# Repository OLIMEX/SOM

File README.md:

=System on Module=

This is the GitHub repository for Olimex System on Module (SOM) boards resources hardware and software.

OLIMEX System-on-Module (SOM) boards are powerful Linux-capable boards. They follow a low-cost modular design which allows rapid product development. Each of these boards has two parts - a main part which nests the processor, the memory and the power control unit; and a peripheral part which contains the USB ports, the video output and most of the connectors. SOM designs are targeted at customers who want to apply custom modifications and own solutions based on a specific processor without having to deal with multi layer PCBs with controlled impedance and BGA assembly. This makes it possible to create simpler boards (that might be manufactured by your local board manufacturer) containing only the peripherals you need with the dimensions and shape suitable for your specific solution.

Both the main part and the peripheral part of the SOM system have support in the official Android and Debian images distributed by Olimex and maintained by Olimex and the Linux community.

The peripheral part of the SOM design is considered Open Source HardWare (OSHW) and the customer has access to the board source files that we used to manufacture it. The part of the design that has the main microcontroller is considered proprietary design and design files would not be shared. The official Android and Debian images released for the SOM boards are open software. We usually try to provide step-by-step instructions on how we have compiled the images. These instructions might be found at the olimex wordpress page. 

If you are looking for the open source hardware design of the processors used, please, check the OLinuXino boards. OLinuXino board designs are fully open source hradware but harder to implement in own solutions and require more of a hardware experience to do so. Nevertheless OLinuXino boards are pretty good choice for evaluating the capabilities of the embedded processors.

At the moment Olimex deals with the following categories of SOM boards:

==Allwinner A13==

==Allwinner A20==

==Texas Instruments AM3352==

==Rockchip RK3188==

==Rockchip RK3328==

==STM STM32MP153==

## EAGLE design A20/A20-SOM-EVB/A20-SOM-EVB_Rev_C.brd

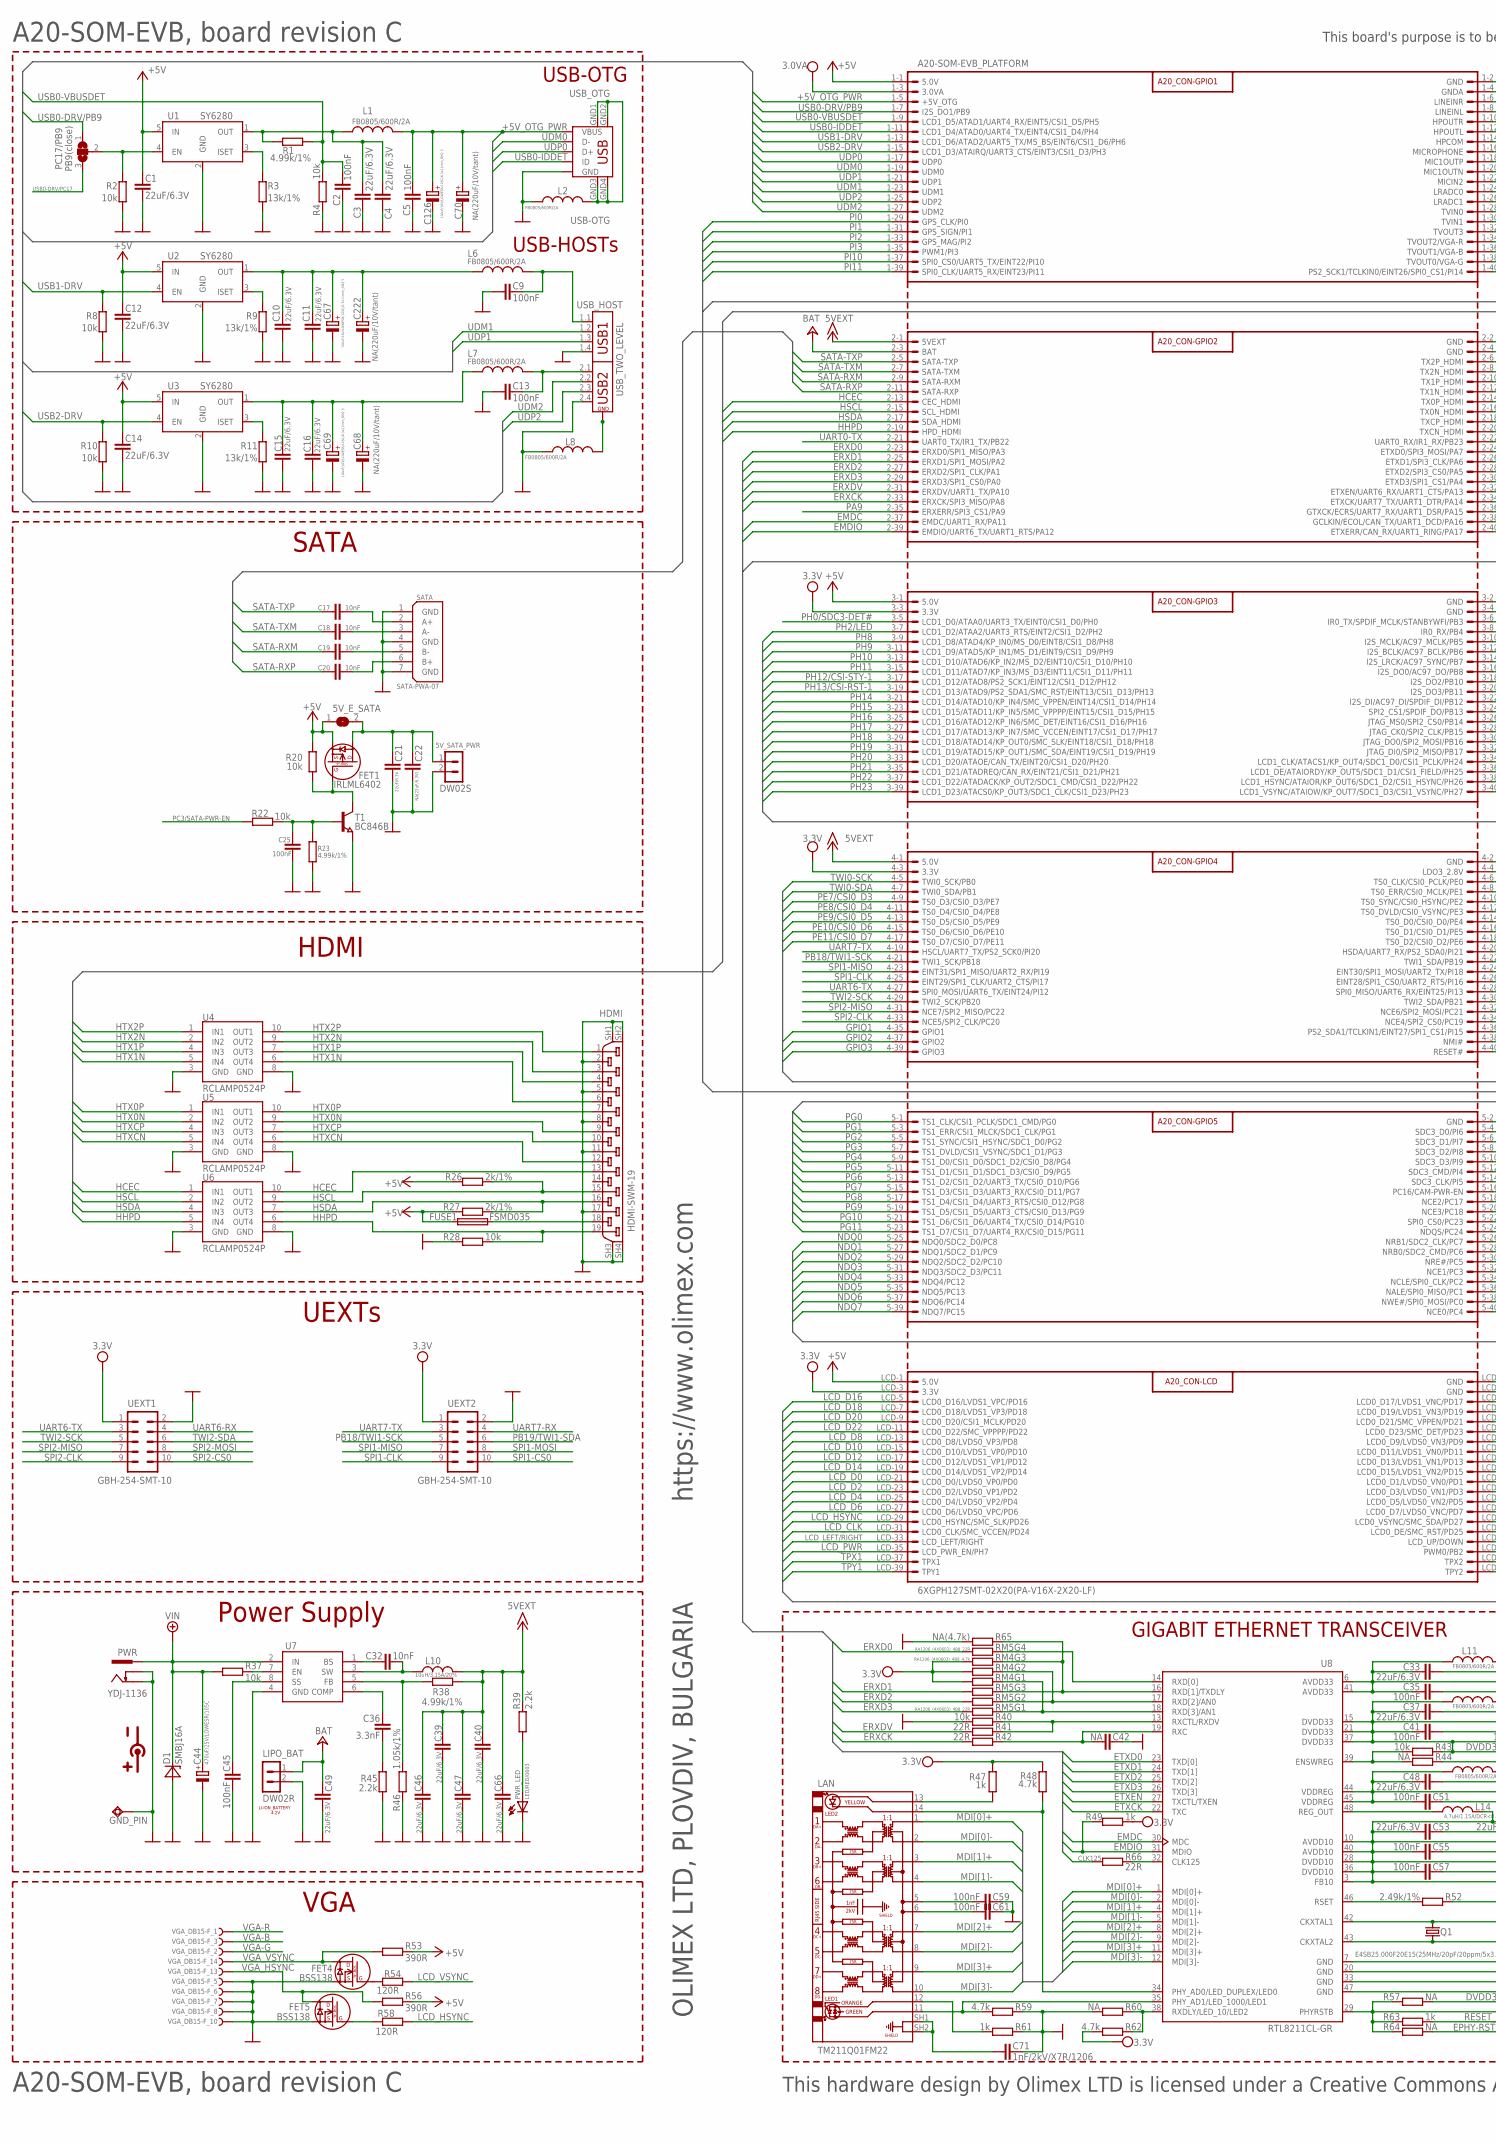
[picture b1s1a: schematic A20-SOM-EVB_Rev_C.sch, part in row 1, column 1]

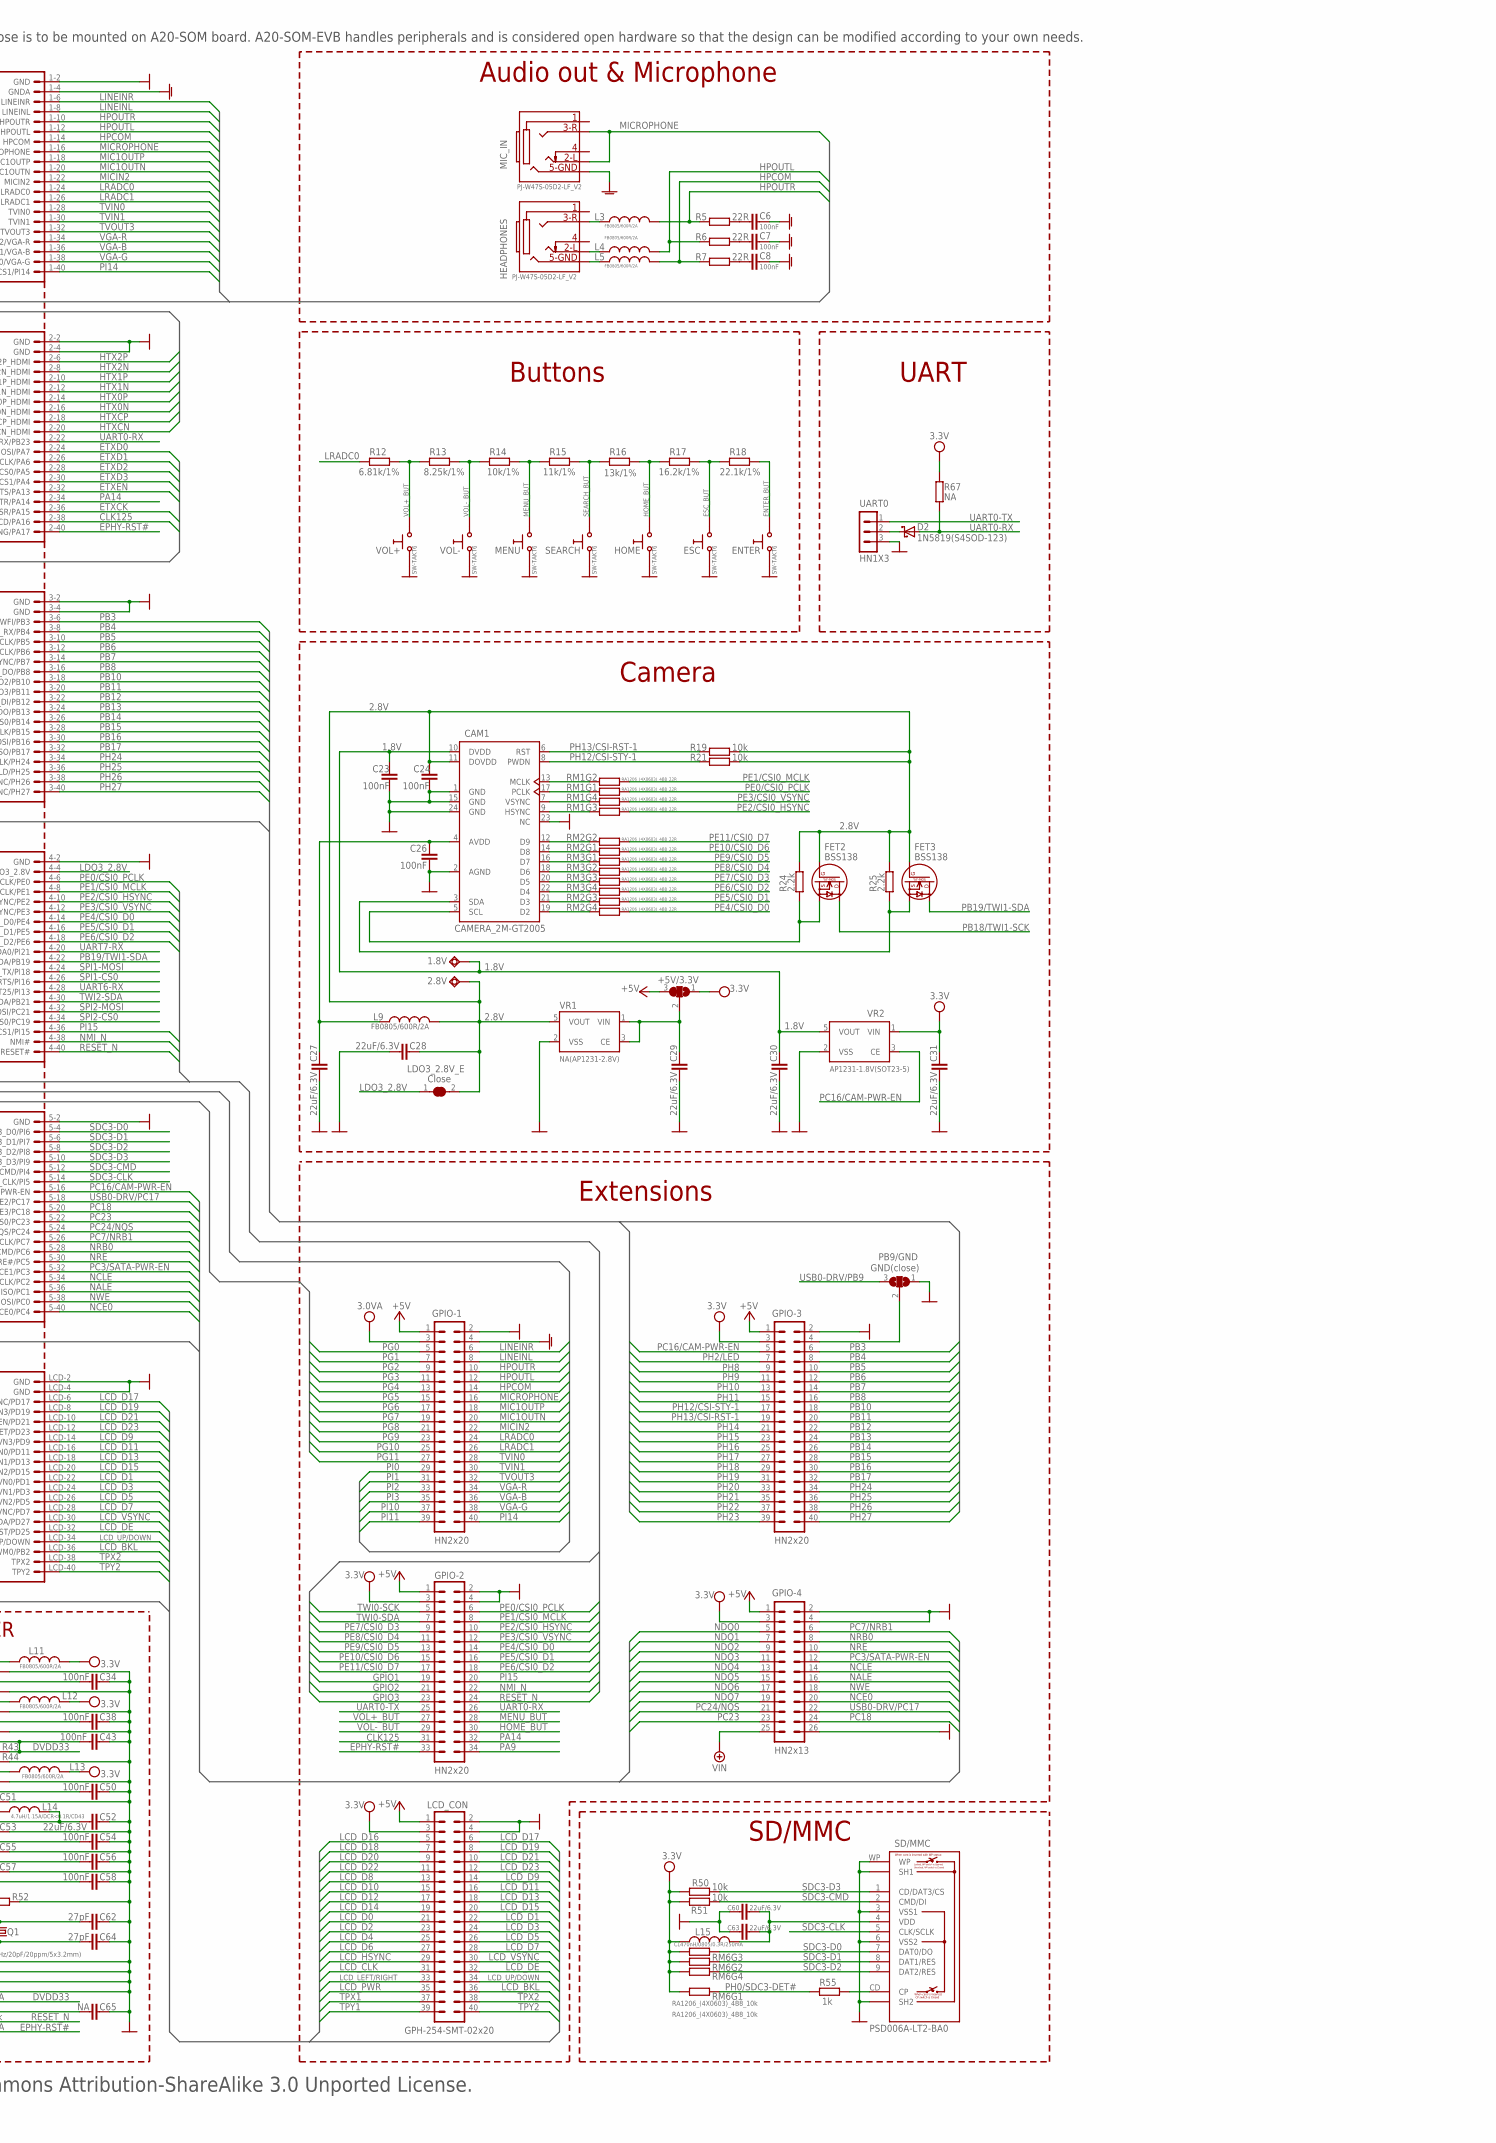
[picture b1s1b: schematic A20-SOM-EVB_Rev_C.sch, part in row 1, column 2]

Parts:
1.8V, 2.8V: TESTPAD80/40; SMD80/40
5V_E_SATA: SJSJ_SMALLER; SJ_1_SMALLER
5V_SATA_PWR: DW02S
+5V/3.3V: SJ2W8; SJ_2_SMALLER_23_TIED
A20-SOM-EVB_PLATFORM: 6XGPH127SMT-02X20(PA-V16X-2X20-LF); A20-SOM-EVB
C1, C3, C4, C10, C11, C12, C14, C15, C16, C21, C27, C28, C29, C30, C31, C33, C37, C39, C40, C46, C47, C48, C49, C52, C53, C60, C63, C66: 22uF/6.3V; C0603_DWS
C2, C5, C6, C7, C8, C9, C13, C23, C24, C25, C26, C34, C35, C38, C41, C43, C45, C50, C51, C54, C55, C56, C57, C58, C59, C61: 100nF; C0603_DWS
C17, C18, C19, C20, C32: 10nF; C0603_DWS
C22: NA(22uF/6.3V); C0603_DWS
C36: 3.3nF; C0603_DWS
C42, C65: NA; C0603_DWS
C44: 470uF/25V/LOWESR/105C; E3,5-8
C62, C64: 27pF; C0603_DWS
C67, C69, C126: 100uF/16V/LOWESR/105C/6.3x11mm_RM2.5; E2,5-6,3
C68, C70, C222: NA(220uF/10V/tant); CT7343
C71: 1nF/2kV/X7R/1206; C1206_5MILS_WS_ISO
CAM1: CAMERA_2M-GT2005; CAM_2M_GT2005
D1: SMBJ16A; DO214AA
D2: 1N5819(S4SOD-123); SOD-123
ENTER: SW-TAKT6; SW-TAKT_6X3.5_SMD
ESC: SW-TAKT6; SW-TAKT_6X3.5_SMD
FET1: IRLML6402; SOT23
FET2, FET3, FET4, FET5: BSS138; SOT23
FUSE1: FSMD035; 1206
GND_PIN: TESTPAD3; TEST_PAD40/70/SQUARE
GPIO-1, GPIO-3: HN2x20; ML40-MALE(GBH-254-SMT-40)
GPIO-2: HN2x20; ML34-MALE(GBH-254-SMT-34)
GPIO-4: HN2x13; ML26-MALE(GBH-254-SMT-26)
HDMI: HDMI-SWM-19
HEADPHONES: PJ-W47S-05D2-LF_V2; PJ-W47S-05D2-LF_5PIN_V2
HOME: SW-TAKT6; SW-TAKT_6X3.5_SMD
L1, L2, L3, L4, L5, L6, L7, L8, L9, L11, L12, L13: FB0805/600R/2A; L0805_5MIL_DWS
L10: 10uH/3.15A/20%; 8X7MM_3131
L14: 4.7uH/1.15A/DCR<0.1R/CD43; CD42(43)
L15: CL470nH/0805/0.3R/250mA; L0805_5MIL_DWS
LAN: TM211Q01FM22; TM211Q01FM22_SH
LCD_CON: GPH-254-SMT-02x20; ML40-MALE(GBH-254-SMT-40)
LDO3_2.8V_E: Close; SJ_1_SMALLER_CLOSE
LIPO_BAT: DW02R
MENU: SW-TAKT6; SW-TAKT_6X3.5_SMD
MIC_IN: PJ-W47S-05D2-LF_V2; PJ-W47S-05D2-LF_5PIN_V2
PB9/GND: GND(close); SJ_2_SMALL
PC17/PB9: PB9(close); SJ_2_SMALL
PWR: YDJ-1136; PWR_JACK_UNI_MILLING
PWR_LED: LED/RED/0603; LED-0603
Q1: E4SB25.000F20E15(25MHz/20pF/20ppm/5x3.2mm); HCX-4S
R1, R23, R38: 4.99k/1%; R0603_5MIL_DWS
R2, R4, R8, R10, R19, R20, R21, R22, R28, R37, R40, R43, R50, R51: 10k; R0603_5MIL_DWS
R3, R9, R11, R16: 13k/1%; R0603_5MIL_DWS
R5, R6, R7, R41, R42, R66: 22R; R0603_5MIL_DWS
R12: 6.81k/1%; R0603_5MIL_DWS
R13: 8.25k/1%; R0603_5MIL_DWS
R14: 10k/1%; R0603_5MIL_DWS
R15: 11k/1%; R0603_5MIL_DWS
R17: 16.2k/1%; R0603_5MIL_DWS
R18: 22.1k/1%; R0603_5MIL_DWS
R24, R25, R39, R45: 2.2k; R0603_5MIL_DWS
R26, R27: 2k/1%; R0603_5MIL_DWS
R44, R57, R60, R64, R67: NA; R0603_5MIL_DWS
R46: 1.05k/1%; R0603_5MIL_DWS
R47, R49, R55, R61, R63: 1k; R0603_5MIL_DWS
R48, R59, R62: 4.7k; R0603_5MIL_DWS
R52: 2.49k/1%; R0603_5MIL_DWS
R53, R56: 390R; R0603_5MIL_DWS
R54, R58: 120R; R0603_5MIL_DWS
R65: NA(4.7k); R0603_5MIL_DWS
RM1, RM2, RM3, RM5: RA1206_(4X0603)_4B8_22R; R_MATRIX_4
RM4: RA1206_(4X0603)_4B8_4.7k; R_MATRIX_4
RM6: RA1206_(4X0603)_4B8_10k; R_MATRIX_4
SATA: SATA-PWA-07
SD/MMC: PSD006A-LT2-BA0; SD_CARD
SEARCH: SW-TAKT6; SW-TAKT_6X3.5_SMD
T1: BC846B; SOT23
U1, U2, U3: SY6280; SOT23-5
U4, U5, U6: RCLAMP0524P; SLP2510P8
U7: MP1482DS; SOIC8
U8: RTL8211CL-GR; LQFP48
UART0: HN1X3
UEXT1, UEXT2: GBH-254-SMT-10; ML10_S
USB_HOST: USB_TWO_LEVEL
USB_OTG: USB-OTG; USB_MINI_9PIN
VGA_DB15-F: VGA15; DB15-F_22MM
VOL+: SW-TAKT6; SW-TAKT_6X3.5_SMD
VOL-: SW-TAKT6; SW-TAKT_6X3.5_SMD
VR1: NA(AP1231-2.8V); SOT-23-5
VR2: AP1231-1.8V(SOT23-5); SOT-23-5

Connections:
1.8V: 1.8V.P$1, C23.1, C30.1, CAM1.10 (DVDD), VR2.5 (VOUT)
2.8V: 2.8V.P$1, C24.1, C28.1, CAM1.11 (DOVDD), FET2.1 (G), FET3.1 (G), L9.2, LDO3_2.8V_E.2, R19.2, R21.2, R24.2, R25.2, VR1.5 (VOUT)
+5V: 5V_E_SATA.1, +5V/3.3V.3, A20-SOM-EVB_PLATFORM.1-1 (5.0V), A20-SOM-EVB_PLATFORM.3-1 (5.0V), A20-SOM-EVB_PLATFORM.LCD-1 (5.0V), C1.1, C12.1, C14.1, FET1.2 (S), FUSE1.1, GPIO-1.1, GPIO-2.1, GPIO-3.1, GPIO-4.1, LCD_CON.1, R20.1, R26.2, R27.2, R53.1, R56.1, U1.5 (IN), U2.5 (IN), U3.5 (IN)
+5V_OTG_PWR: A20-SOM-EVB_PLATFORM.1-5 (+5V_OTG), C5.1, C70.+, C126.+, L1.1, USB_OTG.VBUS
+12V: C44.+, D1.C, GPIO-4.25, PWR.+, R37.1, U7.2 (IN)
+15V: A20-SOM-EVB_PLATFORM.2-1 (5VEXT), A20-SOM-EVB_PLATFORM.4-1 (5.0V), C39.1, C40.1, C46.1, C47.1, C66.1, L10.2, R38.2, R39.1
+24V: A20-SOM-EVB_PLATFORM.2-3 (BAT), C49.2, LIPO_BAT.1
AVDD1: C26.1, C27.1, CAM1.4 (AVDD), L9.1
AVDD33: C33.2, C34.2, C35.2, L11.2, U8.6 (AVDD33), U8.41 (AVDD33)
AVDD/DVDD(1.05V): C52.2, C53.2, C54.2, C55.2, C56.2, C57.2, C58.2, L14.2, U8.3 (FB10), U8.10 (AVDD10), U8.28 (DVDD10), U8.36 (DVDD10), U8.40 (AVDD10)
CLK125: A20-SOM-EVB_PLATFORM.2-38 (GCLKIN/ECOL/CAN_TX/UART1_DCD/PA16), GPIO-2.31, R66.1
DVDD33: C37.2, C38.2, C41.2, C43.2, L12.2, R43.1, R57.1, U8.15 (DVDD33), U8.21 (DVDD33), U8.37 (DVDD33)
EMDC: A20-SOM-EVB_PLATFORM.2-37 (EMDC/UART1_RX/PA11), U8.30 (MDC)
EMDIO: A20-SOM-EVB_PLATFORM.2-39 (EMDIO/UART6_TX/UART1_RTS/PA12), R49.1, U8.31 (MDIO)
ENTER_BUT: ENTER.P$2 (1), R18.2
EPHY-RST#: A20-SOM-EVB_PLATFORM.2-40 (ETXERR/CAN_RX/UART1_RING/PA17), GPIO-2.33, R64.1
ERXCK: A20-SOM-EVB_PLATFORM.2-33 (ERXCK/SPI3_MISO/PA8), R42.2
ERXD0: A20-SOM-EVB_PLATFORM.2-23 (ERXD0/SPI1_MISO/PA3), RM5.4.2 (2)
ERXD1: A20-SOM-EVB_PLATFORM.2-25 (ERXD1/SPI1_MOSI/PA2), RM5.3.2 (2)
ERXD2: A20-SOM-EVB_PLATFORM.2-27 (ERXD2/SPI1_CLK/PA1), RM5.2.2 (2)
ERXD3: A20-SOM-EVB_PLATFORM.2-29 (ERXD3/SPI1_CS0/PA0), RM5.1.2 (2)
ERXDV: A20-SOM-EVB_PLATFORM.2-31 (ERXDV/UART1_TX/PA10), R41.2
ESC_BUT: ESC.P$2 (1), R17.2, R18.1
ETXCK: A20-SOM-EVB_PLATFORM.2-36 (GTXCK/ECRS/UART7_RX/UART1_DSR/PA15), U8.22 (TXC)
ETXD0: A20-SOM-EVB_PLATFORM.2-24 (ETXD0/SPI3_MOSI/PA7), U8.23 (TXD[0])
ETXD1: A20-SOM-EVB_PLATFORM.2-26 (ETXD1/SPI3_CLK/PA6), U8.24 (TXD[1])
ETXD2: A20-SOM-EVB_PLATFORM.2-28 (ETXD2/SPI3_CS0/PA5), U8.25 (TXD[2])
ETXD3: A20-SOM-EVB_PLATFORM.2-30 (ETXD3/SPI1_CS1/PA4), U8.26 (TXD[3])
ETXEN: A20-SOM-EVB_PLATFORM.2-32 (ETXEN/UART6_RX/UART1_CTS/PA13), U8.27 (TXCTL/TXEN)
GND: 5V_SATA_PWR.2, A20-SOM-EVB_PLATFORM.1-2 (GND), A20-SOM-EVB_PLATFORM.2-2 (GND), A20-SOM-EVB_PLATFORM.2-4 (GND), A20-SOM-EVB_PLATFORM.3-2 (GND), A20-SOM-EVB_PLATFORM.3-4 (GND), A20-SOM-EVB_PLATFORM.4-2 (GND), A20-SOM-EVB_PLATFORM.5-2 (GND), A20-SOM-EVB_PLATFORM.LCD-2 (GND), A20-SOM-EVB_PLATFORM.LCD-4 (GND), C1.2, C2.2, C3.2, C4.2, C5.2, C9.2, C10.2, C11.2, C12.2, C13.2, C14.2, C15.2, C16.2, C21.1, C22.1, C23.2, C24.2, C25.2, C26.2, C27.2, C28.2, C29.2, C30.2, C31.2, C33.1, C34.1, C35.1, C37.1, C38.1, C39.2, C40.2, C41.1, C42.2, C43.1, C44.-, C45.2, C46.2, C47.2, C48.1, C49.1, C50.1, C51.1, C52.1, C53.1, C54.1, C55.1, C56.1, C57.1, C58.1, C59.1, C60.1, C61.1, C62.1, C63.1, C64.1, C65.1, C66.2, C67.-, C68.-, C69.-, C70.-, C71.1, C126.-, C222.-, CAM1.1 (GND), CAM1.2 (AGND), CAM1.15 (GND), CAM1.23 (NC), CAM1.24 (GND), D1.A, ENTER.P$1 (0), ESC.P$1 (0), FET4.2 (S), FET5.2 (S), GND_PIN.P$1, GPIO-1.2, GPIO-2.2, GPIO-2.4, GPIO-3.2, GPIO-4.2, GPIO-4.4, GPIO-4.26, HDMI.2, HDMI.5, HDMI.8, HDMI.11, HDMI.17, HDMI.SH1 (20), HDMI.SH2 (21), HDMI.SH3 (22), HDMI.SH4 (23), HOME.P$1 (0), L2.1, L8.1, LCD_CON.2, LCD_CON.4, LIPO_BAT.2, MENU.P$1 (0), PB9/GND.1, PWR.-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
GNDA: A20-SOM-EVB_PLATFORM.1-4 (GNDA), C6.1, C7.1, C8.1, GPIO-1.4, MIC_IN.5
GPIO1: A20-SOM-EVB_PLATFORM.4-35 (GPIO1), GPIO-2.19
GPIO2: A20-SOM-EVB_PLATFORM.4-37 (GPIO2), GPIO-2.21
GPIO3: A20-SOM-EVB_PLATFORM.4-39 (GPIO3), GPIO-2.23
HCEC: A20-SOM-EVB_PLATFORM.2-13 (CEC_HDMI), HDMI.13, U6.1 (IN1), U6.10 (OUT1)
HDMI_5V_SOURCE: FUSE1.2, HDMI.18
HHPD: A20-SOM-EVB_PLATFORM.2-19 (HPD_HDMI), HDMI.19, R28.1, U6.5 (IN4), U6.6 (OUT4)
HOME_BUT: GPIO-2.30, HOME.P$2 (1), R16.2, R17.1
HPCOM: A20-SOM-EVB_PLATFORM.1-14 (HPCOM), GPIO-1.14, L5.1, R7.2
HPOUTL: A20-SOM-EVB_PLATFORM.1-12 (HPOUTL), GPIO-1.12, L4.1, R6.2
HPOUTR: A20-SOM-EVB_PLATFORM.1-10 (HPOUTR), GPIO-1.10, L3.1, R5.2
HSCL: A20-SOM-EVB_PLATFORM.2-15 (SCL_HDMI), HDMI.15, R26.1, U6.2 (IN2), U6.9 (OUT2)
HSDA: A20-SOM-EVB_PLATFORM.2-17 (SDA_HDMI), HDMI.16, R27.1, U6.4 (IN3), U6.7 (OUT3)
HTX0N: A20-SOM-EVB_PLATFORM.2-16 (TX0N_HDMI), HDMI.9, U5.2 (IN2), U5.9 (OUT2)
HTX0P: A20-SOM-EVB_PLATFORM.2-14 (TX0P_HDMI), HDMI.7, U5.1 (IN1), U5.10 (OUT1)
HTX1N: A20-SOM-EVB_PLATFORM.2-12 (TX1N_HDMI), HDMI.6, U4.5 (IN4), U4.6 (OUT4)
HTX1P: A20-SOM-EVB_PLATFORM.2-10 (TX1P_HDMI), HDMI.4, U4.4 (IN3), U4.7 (OUT3)
HTX2N: A20-SOM-EVB_PLATFORM.2-8 (TX2N_HDMI), HDMI.3, U4.2 (IN2), U4.9 (OUT2)
HTX2P: A20-SOM-EVB_PLATFORM.2-6 (TX2P_HDMI), HDMI.1, U4.1 (IN1), U4.10 (OUT1)
HTXCN: A20-SOM-EVB_PLATFORM.2-20 (TXCN_HDMI), HDMI.12, U5.5 (IN4), U5.6 (OUT4)
HTXCP: A20-SOM-EVB_PLATFORM.2-18 (TXCP_HDMI), HDMI.10, U5.4 (IN3), U5.7 (OUT3)
LCD_BKL: A20-SOM-EVB_PLATFORM.LCD-36 (PWM0/PB2), LCD_CON.36
LCD_CLK: A20-SOM-EVB_PLATFORM.LCD-31 (LCD0_CLK/SMC_VCCEN/PD24), LCD_CON.31
LCD_D0: A20-SOM-EVB_PLATFORM.LCD-21 (LCD0_D0/LVDS0_VP0/PD0), LCD_CON.21
LCD_D1: A20-SOM-EVB_PLATFORM.LCD-22 (LCD0_D1/LVDS0_VN0/PD1), LCD_CON.22
LCD_D2: A20-SOM-EVB_PLATFORM.LCD-23 (LCD0_D2/LVDS0_VP1/PD2), LCD_CON.23
LCD_D3: A20-SOM-EVB_PLATFORM.LCD-24 (LCD0_D3/LVDS0_VN1/PD3), LCD_CON.24
LCD_D4: A20-SOM-EVB_PLATFORM.LCD-25 (LCD0_D4/LVDS0_VP2/PD4), LCD_CON.25
LCD_D5: A20-SOM-EVB_PLATFORM.LCD-26 (LCD0_D5/LVDS0_VN2/PD5), LCD_CON.26
LCD_D6: A20-SOM-EVB_PLATFORM.LCD-27 (LCD0_D6/LVDS0_VPC/PD6), LCD_CON.27
LCD_D7: A20-SOM-EVB_PLATFORM.LCD-28 (LCD0_D7/LVDS0_VNC/PD7), LCD_CON.28
LCD_D8: A20-SOM-EVB_PLATFORM.LCD-13 (LCD0_D8/LVDS0_VP3/PD8), LCD_CON.13
LCD_D9: A20-SOM-EVB_PLATFORM.LCD-14 (LCD0_D9/LVDS0_VN3/PD9), LCD_CON.14
LCD_D10: A20-SOM-EVB_PLATFORM.LCD-15 (LCD0_D10/LVDS1_VP0/PD10), LCD_CON.15
LCD_D11: A20-SOM-EVB_PLATFORM.LCD-16 (LCD0_D11/LVDS1_VN0/PD11), LCD_CON.16
LCD_D12: A20-SOM-EVB_PLATFORM.LCD-17 (LCD0_D12/LVDS1_VP1/PD12), LCD_CON.17
LCD_D13: A20-SOM-EVB_PLATFORM.LCD-18 (LCD0_D13/LVDS1_VN1/PD13), LCD_CON.18
LCD_D14: A20-SOM-EVB_PLATFORM.LCD-19 (LCD0_D14/LVDS1_VP2/PD14), LCD_CON.19
LCD_D15: A20-SOM-EVB_PLATFORM.LCD-20 (LCD0_D15/LVDS1_VN2/PD15), LCD_CON.20
LCD_D16: A20-SOM-EVB_PLATFORM.LCD-5 (LCD0_D16/LVDS1_VPC/PD16), LCD_CON.5
LCD_D17: A20-SOM-EVB_PLATFORM.LCD-6 (LCD0_D17/LVDS1_VNC/PD17), LCD_CON.6
LCD_D18: A20-SOM-EVB_PLATFORM.LCD-7 (LCD0_D18/LVDS1_VP3/PD18), LCD_CON.7
LCD_D19: A20-SOM-EVB_PLATFORM.LCD-8 (LCD0_D19/LVDS1_VN3/PD19), LCD_CON.8
LCD_D20: A20-SOM-EVB_PLATFORM.LCD-9 (LCD0_D20/CSI1_MCLK/PD20), LCD_CON.9
LCD_D21: A20-SOM-EVB_PLATFORM.LCD-10 (LCD0_D21/SMC_VPPEN/PD21), LCD_CON.10
LCD_D22: A20-SOM-EVB_PLATFORM.LCD-11 (LCD0_D22/SMC_VPPPP/PD22), LCD_CON.11
LCD_D23: A20-SOM-EVB_PLATFORM.LCD-12 (LCD0_D23/SMC_DET/PD23), LCD_CON.12
LCD_DE: A20-SOM-EVB_PLATFORM.LCD-32 (LCD0_DE/SMC_RST/PD25), LCD_CON.32
LCD_HSYNC: A20-SOM-EVB_PLATFORM.LCD-29 (LCD0_HSYNC/SMC_SLK/PD26), LCD_CON.29, R58.1
LCD_LEFT/RIGHT: A20-SOM-EVB_PLATFORM.LCD-33 (LCD_LEFT/RIGHT), LCD_CON.33
LCD_PWR: A20-SOM-EVB_PLATFORM.LCD-35 (LCD_PWR_EN/PH7), LCD_CON.35
LCD_UP/DOWN: A20-SOM-EVB_PLATFORM.LCD-34 (LCD_UP/DOWN), LCD_CON.34
LCD_VSYNC: A20-SOM-EVB_PLATFORM.LCD-30 (LCD0_VSYNC/SMC_SDA/PD27), LCD_CON.30, R54.1
LDO3_2.8V: A20-SOM-EVB_PLATFORM.4-4 (LDO3_2.8V), LDO3_2.8V_E.1
LINEINL: A20-SOM-EVB_PLATFORM.1-8 (LINEINL), GPIO-1.8
LINEINR: A20-SOM-EVB_PLATFORM.1-6 (LINEINR), GPIO-1.6
LRADC0: A20-SOM-EVB_PLATFORM.1-24 (LRADC0), GPIO-1.24, R12.1
LRADC1: A20-SOM-EVB_PLATFORM.1-26 (LRADC1), GPIO-1.26
MDI[0]+: LAN.1, U8.1 (MDI[0]+)
MDI[0]-: LAN.2, U8.2 (MDI[0]-)
MDI[1]+: LAN.3, U8.4 (MDI[1]+)
MDI[1]-: LAN.4, U8.5 (MDI[1]-)
MDI[2]+: LAN.7, U8.8 (MDI[2]+)
MDI[2]-: LAN.8, U8.9 (MDI[2]-)
MDI[3]+: LAN.9, U8.11 (MDI[3]+)
MDI[3]-: LAN.10, U8.12 (MDI[3]-)
MENU_BUT: GPIO-2.28, MENU.P$2 (1), R14.2, R15.1
MIC1OUTN: A20-SOM-EVB_PLATFORM.1-20 (MIC1OUTN), GPIO-1.20
MIC1OUTP: A20-SOM-EVB_PLATFORM.1-18 (MIC1OUTP), GPIO-1.18
MICIN2: A20-SOM-EVB_PLATFORM.1-22 (MICIN2), GPIO-1.22
MICROPHONE: A20-SOM-EVB_PLATFORM.1-16 (MICROPHONE), GPIO-1.16, MIC_IN.2, MIC_IN.3
unnamed: L2.2, USB_OTG.GND1, USB_OTG.GND2, USB_OTG.GND3, USB_OTG.GND4
unnamed: R3.2, U1.3 (ISET)
unnamed: C3.1, C4.1, L1.2, R1.2, U1.1 (OUT)
unnamed: FET4.1 (G), R54.2
unnamed: FET5.1 (G), R58.2
unnamed: C45.1, U7.8 (SS)
unnamed: R37.2, U7.7 (EN)
unnamed: C32.1, U7.1 (BS)
unnamed: C32.2, L10.1, U7.3 (SW)
unnamed: C36.1, U7.6 (COMP)
unnamed: C36.2, R45.1
unnamed: C71.2, LAN.SH1, LAN.SH2
unnamed: R52.2, U8.46 (RSET)
unnamed: CAM1.3 (SDA), FET3.2 (S), R25.1
unnamed: C62.2, Q1.2, U8.42 (CKXTAL1)
unnamed: C64.2, Q1.1, U8.43 (CKXTAL2)
unnamed: L14.1, U8.48 (REG_OUT)
unnamed: C59.2, LAN.5
unnamed: C65.2, R57.2, R63.2, R64.2, U8.29 (PHYRSTB)
unnamed: C61.2, LAN.6
unnamed: R60.1, R62.1, U8.38 (RXDLY/LED_10/LED2)
unnamed: LAN.12, R61.2
unnamed: LAN.11, R59.2, U8.35 (PHY_AD1/LED_1000/LED1)
unnamed: R43.2, R44.2, U8.39 (ENSWREG)
unnamed: LAN.13, R47.2
unnamed: C42.1, R42.1, U8.19 (RXC)
unnamed: R66.2, U8.32 (CLK125)
unnamed: R40.1, R41.1, U8.13 (RXCTL/RXDV)
unnamed: RM5.4.1 (1), U8.14 (RXD[0])
unnamed: R65.1, RM4.3.1 (1), RM5.3.1 (1), U8.16 (RXD[1]/TXDLY)
unnamed: RM4.2.1 (1), RM5.2.1 (1), U8.17 (RXD[2]/AN0)
unnamed: RM4.1.1 (1), RM5.1.1 (1), U8.18 (RXD[3]/AN1)
unnamed: CAM1.5 (SCL), FET2.2 (S), R24.1
unnamed: CAM1.13 (MCLK), RM1.2.1 (1)
unnamed: CAM1.17 (PCLK), RM1.1.1 (1)
unnamed: CAM1.7 (VSYNC), RM1.4.1 (1)
unnamed: CAM1.9 (HSYNC), RM1.3.1 (1)
unnamed: CAM1.12 (D9), RM2.2.1 (1)
unnamed: CAM1.14 (D8), RM2.1.1 (1)
unnamed: CAM1.16 (D7), RM3.1.1 (1)
unnamed: CAM1.18 (D6), RM3.2.1 (1)
unnamed: CAM1.20 (D5), RM3.3.1 (1)
unnamed: CAM1.22 (D4), RM3.4.1 (1)
unnamed: CAM1.21 (D3), RM2.3.1 (1)
unnamed: CAM1.19 (D2), RM2.4.1 (1)
unnamed: LAN.14, R48.1, U8.34 (PHY_AD0/LED_DUPLEX/LED0)
unnamed: C7.2, R6.1
unnamed: C8.2, R7.1
unnamed: C6.2, R5.1
unnamed: HEADPHONES.5, L5.2
unnamed: HEADPHONES.2, L4.2
unnamed: HEADPHONES.3, L3.2
unnamed: C25.1, R22.1, R23.2, T1.1 (B)
unnamed: FET1.1 (G), R20.2, T1.3 (C)
unnamed: 5V_E_SATA.2, 5V_SATA_PWR.1, C21.2, C22.2, FET1.3 (D)
unnamed: D2.C, UART0.2
unnamed: +5V/3.3V.2, C29.1, VR1.1 (VIN), VR1.3 (CE)
unnamed: GPIO-3.4, PB9/GND.2
unnamed: PC17/PB9.2, R2.2, U1.4 (EN)
unnamed: R38.1, R46.1, U7.5 (FB)
unnamed: R9.2, U2.3 (ISET)
unnamed: C17.2, SATA.2 (A+)
unnamed: C9.1, L6.2, USB_HOST.1.1
unnamed: C18.2, SATA.3 (A-)
unnamed: C19.2, SATA.5 (B-)
unnamed: C20.2, SATA.6 (B+)
unnamed: PWR_LED.A, R39.2
unnamed: R11.2, U3.3 (ISET)
unnamed: R55.1, SD/MMC.CD (CP)
unnamed: C10.1, C11.1, C67.+, C222.+, L6.1, U2.1 (OUT)
unnamed: L8.2, USB_HOST.GND1, USB_HOST.GND2, USB_HOST.GND3, USB_HOST.GND4
unnamed: C13.1, L7.2, USB_HOST.2.1
unnamed: C15.1, C16.1, C68.+, C69.+, L7.1, U3.1 (OUT)
NALE: A20-SOM-EVB_PLATFORM.5-36 (NALE/SPI0_MISO/PC1), GPIO-4.16
NCE0: A20-SOM-EVB_PLATFORM.5-40 (NCE0/PC4), GPIO-4.20
NCLE: A20-SOM-EVB_PLATFORM.5-34 (NCLE/SPI0_CLK/PC2), GPIO-4.14
NDQ0: A20-SOM-EVB_PLATFORM.5-25 (NDQ0/SDC2_D0/PC8), GPIO-4.5
NDQ1: A20-SOM-EVB_PLATFORM.5-27 (NDQ1/SDC2_D1/PC9), GPIO-4.7
NDQ2: A20-SOM-EVB_PLATFORM.5-29 (NDQ2/SDC2_D2/PC10), GPIO-4.9
NDQ3: A20-SOM-EVB_PLATFORM.5-31 (NDQ3/SDC2_D3/PC11), GPIO-4.11
NDQ4: A20-SOM-EVB_PLATFORM.5-33 (NDQ4/PC12), GPIO-4.13
NDQ5: A20-SOM-EVB_PLATFORM.5-35 (NDQ5/PC13), GPIO-4.15
NDQ6: A20-SOM-EVB_PLATFORM.5-37 (NDQ6/PC14), GPIO-4.17
NDQ7: A20-SOM-EVB_PLATFORM.5-39 (NDQ7/PC15), GPIO-4.19
NMI_N: A20-SOM-EVB_PLATFORM.4-38 (NMI#), GPIO-2.22
NRB0: A20-SOM-EVB_PLATFORM.5-28 (NRB0/SDC2_CMD/PC6), GPIO-4.8
NRE: A20-SOM-EVB_PLATFORM.5-30 (NRE#/PC5), GPIO-4.10
NWE: A20-SOM-EVB_PLATFORM.5-38 (NWE#/SPI0_MOSI/PC0), GPIO-4.18
PA9: A20-SOM-EVB_PLATFORM.2-35 (ERXERR/SPI3_CS1/PA9), GPIO-2.34
PA14: A20-SOM-EVB_PLATFORM.2-34 (ETXCK/UART7_TX/UART1_DTR/PA14), GPIO-2.32
PB3: A20-SOM-EVB_PLATFORM.3-6 (IR0_TX/SPDIF_MCLK/STANBYWFI/PB3), GPIO-3.6
PB4: A20-SOM-EVB_PLATFORM.3-8 (IR0_RX/PB4), GPIO-3.8
PB5: A20-SOM-EVB_PLATFORM.3-10 (I2S_MCLK/AC97_MCLK/PB5), GPIO-3.10
PB6: A20-SOM-EVB_PLATFORM.3-12 (I2S_BCLK/AC97_BCLK/PB6), GPIO-3.12
PB7: A20-SOM-EVB_PLATFORM.3-14 (I2S_LRCK/AC97_SYNC/PB7), GPIO-3.14
PB8: A20-SOM-EVB_PLATFORM.3-16 (I2S_DO0/AC97_DO/PB8), GPIO-3.16
PB10: A20-SOM-EVB_PLATFORM.3-18 (I2S_DO2/PB10), GPIO-3.18
PB11: A20-SOM-EVB_PLATFORM.3-20 (I2S_DO3/PB11), GPIO-3.20
PB12: A20-SOM-EVB_PLATFORM.3-22 (I2S_DI/AC97_DI/SPDIF_DI/PB12), GPIO-3.22
PB13: A20-SOM-EVB_PLATFORM.3-24 (SPI2_CS1/SPDIF_DO/PB13), GPIO-3.24
PB14: A20-SOM-EVB_PLATFORM.3-26 (JTAG_MS0/SPI2_CS0/PB14), GPIO-3.26
PB15: A20-SOM-EVB_PLATFORM.3-28 (JTAG_CK0/SPI2_CLK/PB15), GPIO-3.28
PB16: A20-SOM-EVB_PLATFORM.3-30 (JTAG_DO0/SPI2_MOSI/PB16), GPIO-3.30
PB17: A20-SOM-EVB_PLATFORM.3-32 (JTAG_DI0/SPI2_MISO/PB17), GPIO-3.32
PB18/TWI1-SCK: A20-SOM-EVB_PLATFORM.4-21 (TWI1_SCK/PB18), FET2.3 (D), UEXT2.5
PB19/TWI1-SDA: A20-SOM-EVB_PLATFORM.4-22 (TWI1_SDA/PB19), FET3.3 (D), UEXT2.6
PC3/SATA-PWR-EN: A20-SOM-EVB_PLATFORM.5-32 (NCE1/PC3), GPIO-4.12, R22.2
PC7/NRB1: A20-SOM-EVB_PLATFORM.5-26 (NRB1/SDC2_CLK/PC7), GPIO-4.6
PC16/CAM-PWR-EN: A20-SOM-EVB_PLATFORM.5-16 (PC16/CAM-PWR-EN), GPIO-3.5, VR2.3 (CE)
PC18: A20-SOM-EVB_PLATFORM.5-20 (NCE3/PC18), GPIO-4.24
PC23: A20-SOM-EVB_PLATFORM.5-22 (SPI0_CS0/PC23), GPIO-4.23
PC24/NQS: A20-SOM-EVB_PLATFORM.5-24 (NDQS/PC24), GPIO-4.21
PE0/CSI0_PCLK: A20-SOM-EVB_PLATFORM.4-6 (TS0_CLK/CSI0_PCLK/PE0), GPIO-2.6, RM1.1.2 (2)
PE1/CSI0_MCLK: A20-SOM-EVB_PLATFORM.4-8 (TS0_ERR/CSI0_MCLK/PE1), GPIO-2.8, RM1.2.2 (2)
PE2/CSI0_HSYNC: A20-SOM-EVB_PLATFORM.4-10 (TS0_SYNC/CSI0_HSYNC/PE2), GPIO-2.10, RM1.3.2 (2)
PE3/CSI0_VSYNC: A20-SOM-EVB_PLATFORM.4-12 (TS0_DVLD/CSI0_VSYNC/PE3), GPIO-2.12, RM1.4.2 (2)
PE4/CSI0_D0: A20-SOM-EVB_PLATFORM.4-14 (TS0_D0/CSI0_D0/PE4), GPIO-2.14, RM2.4.2 (2)
PE5/CSI0_D1: A20-SOM-EVB_PLATFORM.4-16 (TS0_D1/CSI0_D1/PE5), GPIO-2.16, RM2.3.2 (2)
PE6/CSI0_D2: A20-SOM-EVB_PLATFORM.4-18 (TS0_D2/CSI0_D2/PE6), GPIO-2.18, RM3.4.2 (2)
PE7/CSI0_D3: A20-SOM-EVB_PLATFORM.4-9 (TS0_D3/CSI0_D3/PE7), GPIO-2.9, RM3.3.2 (2)
PE8/CSI0_D4: A20-SOM-EVB_PLATFORM.4-11 (TS0_D4/CSI0_D4/PE8), GPIO-2.11, RM3.2.2 (2)
PE9/CSI0_D5: A20-SOM-EVB_PLATFORM.4-13 (TS0_D5/CSI0_D5/PE9), GPIO-2.13, RM3.1.2 (2)
PE10/CSI0_D6: A20-SOM-EVB_PLATFORM.4-15 (TS0_D6/CSI0_D6/PE10), GPIO-2.15, RM2.1.2 (2)
PE11/CSI0_D7: A20-SOM-EVB_PLATFORM.4-17 (TS0_D7/CSI0_D7/PE11), GPIO-2.17, RM2.2.2 (2)
PG0: A20-SOM-EVB_PLATFORM.5-1 (TS1_CLK/CSI1_PCLK/SDC1_CMD/PG0), GPIO-1.5
PG1: A20-SOM-EVB_PLATFORM.5-3 (TS1_ERR/CSI1_MLCK/SDC1_CLK/PG1), GPIO-1.7
PG2: A20-SOM-EVB_PLATFORM.5-5 (TS1_SYNC/CSI1_HSYNC/SDC1_D0/PG2), GPIO-1.9
PG3: A20-SOM-EVB_PLATFORM.5-7 (TS1_DVLD/CSI1_VSYNC/SDC1_D1/PG3), GPIO-1.11
PG4: A20-SOM-EVB_PLATFORM.5-9 (TS1_D0/CSI1_D0/SDC1_D2/CSI0_D8/PG4), GPIO-1.13
PG5: A20-SOM-EVB_PLATFORM.5-11 (TS1_D1/CSI1_D1/SDC1_D3/CSI0_D9/PG5), GPIO-1.15
PG6: A20-SOM-EVB_PLATFORM.5-13 (TS1_D2/CSI1_D2/UART3_TX/CSI0_D10/PG6), GPIO-1.17
PG7: A20-SOM-EVB_PLATFORM.5-15 (TS1_D3/CSI1_D3/UART3_RX/CSI0_D11/PG7), GPIO-1.19
PG8: A20-SOM-EVB_PLATFORM.5-17 (TS1_D4/CSI1_D4/UART3_RTS/CSI0_D12/PG8), GPIO-1.21
PG9: A20-SOM-EVB_PLATFORM.5-19 (TS1_D5/CSI1_D5/UART3_CTS/CSI0_D13/PG9), GPIO-1.23
PG10: A20-SOM-EVB_PLATFORM.5-21 (TS1_D6/CSI1_D6/UART4_TX/CSI0_D14/PG10), GPIO-1.25
PG11: A20-SOM-EVB_PLATFORM.5-23 (TS1_D7/CSI1_D7/UART4_RX/CSI0_D15/PG11), GPIO-1.27
PH0/SDC3-DET#: A20-SOM-EVB_PLATFORM.3-5 (LCD1_D0/ATAA0/UART3_TX/EINT0/CSI1_D0/PH0), R55.2, RM6.1.1 (1)
PH2/LED: A20-SOM-EVB_PLATFORM.3-7 (LCD1_D2/ATAA2/UART3_RTS/EINT2/CSI1_D2/P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), GPIO-3.7
PH8: A20-SOM-EVB_PLATFORM.3-9 (LCD1_D8/ATAD4/KP_IN0/MS_D0/EINT8/CSI1_D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), GPIO-3.9
PH9: A20-SOM-EVB_PLATFORM.3-11 (LCD1_D9/ATAD5/KP_IN1/MS_D1/EINT9/CSI1_D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), GPIO-3.11
PH10: A20-SOM-EVB_PLATFORM.3-13 (LCD1_D10/ATAD6/KP_IN2/MS_D2/EINT10/CSI1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), GPIO-3.13
PH11: A20-SOM-EVB_PLATFORM.3-15 (LCD1_D11/ATAD7/KP_IN3/MS_D3/EINT11/CSI1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), GPIO-3.15
PH12/CSI-STY-1: A20-SOM-EVB_PLATFORM.3-17 (LCD1_D12/ATAD8/PS2_SCK1/EINT12/CSI1_D12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), CAM1.8 (PWDN), GPIO-3.17, R21.1
PH13/CSI-RST-1: A20-SOM-EVB_PLATFORM.3-19 (LCD1_D13/ATAD9/PS2_SDA1/SMC_RST/EINT13/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), CAM1.6 (RST), GPIO-3.19, R19.1
PH14: A20-SOM-EVB_PLATFORM.3-21 (LCD1_D14/ATAD10/KP_IN4/SMC_VPPEN/EINT14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), GPIO-3.21
PH15: A20-SOM-EVB_PLATFORM.3-23 (LCD1_D15/ATAD11/KP_IN5/SMC_VPPPP/EINT15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), GPIO-3.23
PH16: A20-SOM-EVB_PLATFORM.3-25 (LCD1_D16/ATAD12/KP_IN6/SMC_DET/EINT16/C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), GPIO-3.25
PH17: A20-SOM-EVB_PLATFORM.3-27 (LCD1_D17/ATAD13/KP_IN7/SMC_VCCEN/EINT17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), GPIO-3.27
PH18: A20-SOM-EVB_PLATFORM.3-29 (LCD1_D18/ATAD14/KP_OUT0/SMC_SLK/EINT18/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), GPIO-3.29
PH19: A20-SOM-EVB_PLATFORM.3-31 (LCD1_D19/ATAD15/KP_OUT1/SMC_SDA/EINT19/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), GPIO-3.31
PH20: A20-SOM-EVB_PLATFORM.3-33 (LCD1_D20/ATAOE/CAN_TX/EINT20/CSI1_D20/P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), GPIO-3.33
PH21: A20-SOM-EVB_PLATFORM.3-35 (LCD1_D21/ATADREQ/CAN_RX/EINT21/CSI1_D21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), GPIO-3.35
PH22: A20-SOM-EVB_PLATFORM.3-37 (LCD1_D22/ATADACK/KP_OUT2/SDC1_CMD/CSI1_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), GPIO-3.37
PH23: A20-SOM-EVB_PLATFORM.3-39 (LCD1_D23/ATACS0/KP_OUT3/SDC1_CLK/CSI1_D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), GPIO-3.39
PH24: A20-SOM-EVB_PLATFORM.3-34 (LCD1_CLK/ATACS1/KP_OUT4/SDC1_D0/CSI1_PC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), GPIO-3.34
PH25: A20-SOM-EVB_PLATFORM.3-36 (LCD1_DE/ATAIORDY/KP_OUT5/SDC1_D1/CSI1_F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), GPIO-3.36
PH26: A20-SOM-EVB_PLATFORM.3-38 (LCD1_HSYNC/ATAIOR/KP_OUT6/SDC1_D2/CSI1_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), GPIO-3.38
PH27: A20-SOM-EVB_PLATFORM.3-40 (LCD1_VSYNC/ATAIOW/KP_OUT7/SDC1_D3/CSI1_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), GPIO-3.40
PI0: A20-SOM-EVB_PLATFORM.1-29 (GPS_CLK/PI0), GPIO-1.29
PI1: A20-SOM-EVB_PLATFORM.1-31 (GPS_SIGN/PI1), GPIO-1.31
PI2: A20-SOM-EVB_PLATFORM.1-33 (GPS_MAG/PI2), GPIO-1.33
PI3: A20-SOM-EVB_PLATFORM.1-35 (PWM1/PI3), GPIO-1.35
PI10: A20-SOM-EVB_PLATFORM.1-37 (SPI0_CS0/UART5_TX/EINT22/PI10), GPIO-1.37
PI11: A20-SOM-EVB_PLATFORM.1-39 (SPI0_CLK/UART5_RX/EINT23/PI11), GPIO-1.39
PI14: A20-SOM-EVB_PLATFORM.1-40 (PS2_SCK1/TCLKIN0/EINT26/SPI0_CS1/PI14), GPIO-1.40
PI15: A20-SOM-EVB_PLATFORM.4-36 (PS2_SDA1/TCLKIN1/EINT27/SPI1_CS1/PI15), GPIO-2.20
RESET_N: A20-SOM-EVB_PLATFORM.4-40 (RESET#), GPIO-2.24, R63.1
SATA-RXM: A20-SOM-EVB_PLATFORM.2-9 (SATA-RXM), C19.1
SATA-RXP: A20-SOM-EVB_PLATFORM.2-11 (SATA-RXP), C20.1
SATA-TXM: A20-SOM-EVB_PLATFORM.2-7 (SATA-TXM), C18.1
SATA-TXP: A20-SOM-EVB_PLATFORM.2-5 (SATA-TXP), C17.1
SDC3-CLK: A20-SOM-EVB_PLATFORM.5-14 (SDC3_CLK/PI5), SD/MMC.5 (CLK/SCLK)
SDC3-CMD: A20-SOM-EVB_PLATFORM.5-12 (SDC3_CMD/PI4), R51.1, SD/MMC.2 (CMD/DI)
SDC3-D0: A20-SOM-EVB_PLATFORM.5-4 (SDC3_D0/PI6), RM6.3.1 (1), SD/MMC.7 (DAT0/DO)
SDC3-D1: A20-SOM-EVB_PLATFORM.5-6 (SDC3_D1/PI7), RM6.2.1 (1), SD/MMC.8 (DAT1/RES)
SDC3-D2: A20-SOM-EVB_PLATFORM.5-8 (SDC3_D2/PI8), RM6.4.1 (1), SD/MMC.9 (DAT2/RES)
SDC3-D3: A20-SOM-EVB_PLATFORM.5-10 (SDC3_D3/PI9), R50.1, SD/MMC.1 (CD/DAT3/CS)
SD_VCC1: C60.2, C63.2, L15.2, SD/MMC.4 (VDD)
SEARCH_BUT: R15.2, R16.1, SEARCH.P$2 (1)
SPI1-CLK: A20-SOM-EVB_PLATFORM.4-25 (EINT29/SPI1_CLK/UART2_CTS/PI17), UEXT2.9
SPI1-CS0: A20-SOM-EVB_PLATFORM.4-26 (EINT28/SPI1_CS0/UART2_RTS/PI16), UEXT2.10
SPI1-MISO: A20-SOM-EVB_PLATFORM.4-23 (EINT31/SPI1_MISO/UART2_RX/PI19), UEXT2.7
SPI1-MOSI: A20-SOM-EVB_PLATFORM.4-24 (EINT30/SPI1_MOSI/UART2_TX/PI18), UEXT2.8
SPI2-CLK: A20-SOM-EVB_PLATFORM.4-33 (NCE5/SPI2_CLK/PC20), UEXT1.9
SPI2-CS0: A20-SOM-EVB_PLATFORM.4-34 (NCE4/SPI2_CS0/PC19), UEXT1.10
SPI2-MISO: A20-SOM-EVB_PLATFORM.4-31 (NCE7/SPI2_MISO/PC22), UEXT1.7
SPI2-MOSI: A20-SOM-EVB_PLATFORM.4-32 (NCE6/SPI2_MOSI/PC21), UEXT1.8
TPX1: A20-SOM-EVB_PLATFORM.LCD-37 (TPX1), LCD_CON.37
TPX2: A20-SOM-EVB_PLATFORM.LCD-38 (TPX2), LCD_CON.38
TPY1: A20-SOM-EVB_PLATFORM.LCD-39 (TPY1), LCD_CON.39
TPY2: A20-SOM-EVB_PLATFORM.LCD-40 (TPY2), LCD_CON.40
TVIN0: A20-SOM-EVB_PLATFORM.1-28 (TVIN0), GPIO-1.28
TVIN1: A20-SOM-EVB_PLATFORM.1-30 (TVIN1), GPIO-1.30
TVOUT3: A20-SOM-EVB_PLATFORM.1-32 (TVOUT3), GPIO-1.32
TWI0-SCK: A20-SOM-EVB_PLATFORM.4-5 (TWI0_SCK/PB0), GPIO-2.5
TWI0-SDA: A20-SOM-EVB_PLATFORM.4-7 (TWI0_SDA/PB1), GPIO-2.7
TWI2-SCK: A20-SOM-EVB_PLATFORM.4-29 (TWI2_SCK/PB20), UEXT1.5
TWI2-SDA: A20-SOM-EVB_PLATFORM.4-30 (TWI2_SDA/PB21), UEXT1.6
UART0-RX: A20-SOM-EVB_PLATFORM.2-22 (UART0_RX/IR1_RX/PB23), D2.A, GPIO-2.26, R67.1
UART0-TX: A20-SOM-EVB_PLATFORM.2-21 (UART0_TX/IR1_TX/PB22), GPIO-2.25, UART0.1
UART6-RX: A20-SOM-EVB_PLATFORM.4-28 (SPI0_MISO/UART6_RX/EINT25/PI13), UEXT1.4
UART6-TX: A20-SOM-EVB_PLATFORM.4-27 (SPI0_MOSI/UART6_TX/EINT24/PI12), UEXT1.3
UART7-RX: A20-SOM-EVB_PLATFORM.4-20 (HSDA/UART7_RX/PS2_SDA0/PI21), UEXT2.4
UART7-TX: A20-SOM-EVB_PLATFORM.4-19 (HSCL/UART7_TX/PS2_SCK0/PI20), UEXT2.3
UDM0: A20-SOM-EVB_PLATFORM.1-19 (UDM0), USB_OTG.D-
UDM1: A20-SOM-EVB_PLATFORM.1-23 (UDM1), USB_HOST.1.2
UDM2: A20-SOM-EVB_PLATFORM.1-27 (UDM2), USB_HOST.2.2
UDP0: A20-SOM-EVB_PLATFORM.1-17 (UDP0), USB_OTG.D+
UDP1: A20-SOM-EVB_PLATFORM.1-21 (UDP1), USB_HOST.1.3
UDP2: A20-SOM-EVB_PLATFORM.1-25 (UDP2), USB_HOST.2.3
USB0-DRV/PB9: A20-SOM-EVB_PLATFORM.1-7 (I2S_DO1/PB9), PB9/GND.3, PC17/PB9.1
USB0-DRV/PC17: A20-SOM-EVB_PLATFORM.5-18 (NCE2/PC17), GPIO-4.22, PC17/PB9.3
USB0-IDDET: A20-SOM-EVB_PLATFORM.1-11 (LCD1_D4/ATAD0/UART4_TX/EINT4/CSI1_D4/PH4), USB_OTG.ID
USB0-VBUSDET: A20-SOM-EVB_PLATFORM.1-9 (LCD1_D5/ATAD1/UART4_RX/EINT5/CSI1_D5/PH5), C2.1, R1.1, R4.2
USB1-DRV: A20-SOM-EVB_PLATFORM.1-13 (LCD1_D6/ATAD2/UART5_TX/MS_BS/EINT6/CSI1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), R8.2, U2.4 (EN)
USB2-DRV: A20-SOM-EVB_PLATFORM.1-15 (LCD1_D3/ATAIRQ/UART3_CTS/EINT3/CSI1_D3/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), R10.2, U3.4 (EN)
VCC: +5V/3.3V.1, A20-SOM-EVB_PLATFORM.3-3 (3.3V), A20-SOM-EVB_PLATFORM.4-3 (3.3V), A20-SOM-EVB_PLATFORM.LCD-3 (3.3V), C31.1, GPIO-2.3, GPIO-3.3, GPIO-4.3, L11.1, L12.1, L13.1, L15.1, LCD_CON.3, R47.1, R48.2, R49.2, R50.2, R51.2, R62.2, R67.2, RM4.1.2 (2), RM4.2.2 (2), RM4.3.2 (2), RM6.1.2 (2), RM6.2.2 (2), RM6.3.2 (2), RM6.4.2 (2), UEXT1.1, UEXT2.1, VR2.1 (VIN)
VDDREG: C48.2, C50.2, C51.2, L13.2, U8.44 (VDDREG), U8.45 (VDDREG)
VGA-B: A20-SOM-EVB_PLATFORM.1-36 (TVOUT1/VGA-B), GPIO-1.36, VGA_DB15-F.3 (F)
VGA-G: A20-SOM-EVB_PLATFORM.1-38 (TVOUT0/VGA-G), GPIO-1.38, VGA_DB15-F.2 (F)
VGA-R: A20-SOM-EVB_PLATFORM.1-34 (TVOUT2/VGA-R), GPIO-1.34, VGA_DB15-F.1 (F)
VGA_HSYNC: FET5.3 (D), R56.2, VGA_DB15-F.13 (F)
VGA_VSYNC: FET4.3 (D), R53.2, VGA_DB15-F.14 (F)
VOL+_BUT: GPIO-2.27, R12.2, R13.1, VOL+.P$2 (1)
VOL-_BUT: GPIO-2.29, R13.2, R14.1, VOL-.P$2 (1)
VPP: A20-SOM-EVB_PLATFORM.1-3 (3.0VA), GPIO-1.3

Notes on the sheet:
SD/MMC
HDMI
USB-OTG
USB-HOSTs
VGA
Power Supply
UEXTs
GIGABIT ETHERNET TRANSCEIVER
LI-ION_BATTERY
Extensions
4.2V
SATA
Camera
Buttons
Audio out & Microphone
UART
A20-SOM-EVB, board revision C
OLIMEX LTD, PLOVDIV, BULGARIA
https://www.olimex.com
This board's purpose is to be mounted on A20-SOM board. A20-SOM-EVB handles peripherals and is considered open hardware so that the design can be modified according to your own needs.
This hardware design by Olimex LTD is licensed under a Creative Commons Attribution-ShareAlike 3.0 Unported License.

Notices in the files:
A20/A20-SOM-EVB/A20-SOM-EVB_Rev_C.brd:
(C) 2014
